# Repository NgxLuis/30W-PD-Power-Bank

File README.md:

# High Performance 30W PD Power Bank (3S 21700)

A professional-grade, high-performance 30W Power Delivery (PD) power bank design. This project features a modular architecture combining fast charging, robust multi-cell battery management, and an efficient synchronous buck controller.

## Technical Specifications

- **Input:** 15W Fast Charging (12.6V/1.2A) via IP2326 Boost Converter architecture.
- **Output:** Up to 30W Power Delivery (PD) via SW3518 Buck Converter.
- **Battery Configuration:** 3S (3 cell) 21700 Li-ion battery pack (approx. 5000mAh/cell, 50Wh total energy capacity).
- **Protection & Management:** Low-side switching BMS powered by BM3451, supporting over-charge, over-discharge, short-circuit, over-current protection, and active cell balancing.
- **Target BOM Budget:** Under 500,000 VND.

## System Architecture & Current Flow

### 1. Charging Mode (Input)
- **IC utilized:** IP2326 (configured for a 3S cell system via a 1kΩ resistor).
- **Current Pathway:** USB-C Input → IP2326 VIN → Internal Boost Switching (via Inductor L2) → VOUT → Battery Cell Positive (+) → Through 3S Battery Cells → Battery Cell Negative (-) → BMS Protection MOSFETs → System Ground (P-) → IP2326 PGND → USB-C Ground return.

### 2. Discharging Mode (Output)
- **IC utilized:** SW3518 (Synchronous Buck Controller).
- **Current Pathway:** Battery Positive (+) → SW3518 VIN → Internal Synchronous Buck Switching (High/Low-side MOSFETs) → Buck Inductor (L1) → Current Shunt Resistor → USB Type-C Port → External Load/Device → Device Ground Return → System Ground (P-) → BMS Protection MOSFETs → Battery Negative (-).

## Hardware Component Configurations
- **IP2326 Charge Current:** Configured via `RISET = 75kΩ` at the ISET pin to cap maximum input charge current at 1.2A.
- **Inductor L2 (Boost):** Requires a saturation current ($I_{SAT}$) of at least 5A.
- **BMS Protection MOSFETs:** Dual NMOS configured with $I_D > 10A$ and ultra-low $R_{DS(on)} < 10mΩ$ to ensure thermal stability and prevent burnout during continuous 3.33A discharge cycles (calculated at the 9V lower cutoff limit).

## Repository Directory Structure
- `/Hardware`: Contains the KiCad schematic (`.kicad_sch`), PCB layout (`.kicad_pcb`), and manufacturing files.
- `/Documentation`: Contains component datasheets and reference files.

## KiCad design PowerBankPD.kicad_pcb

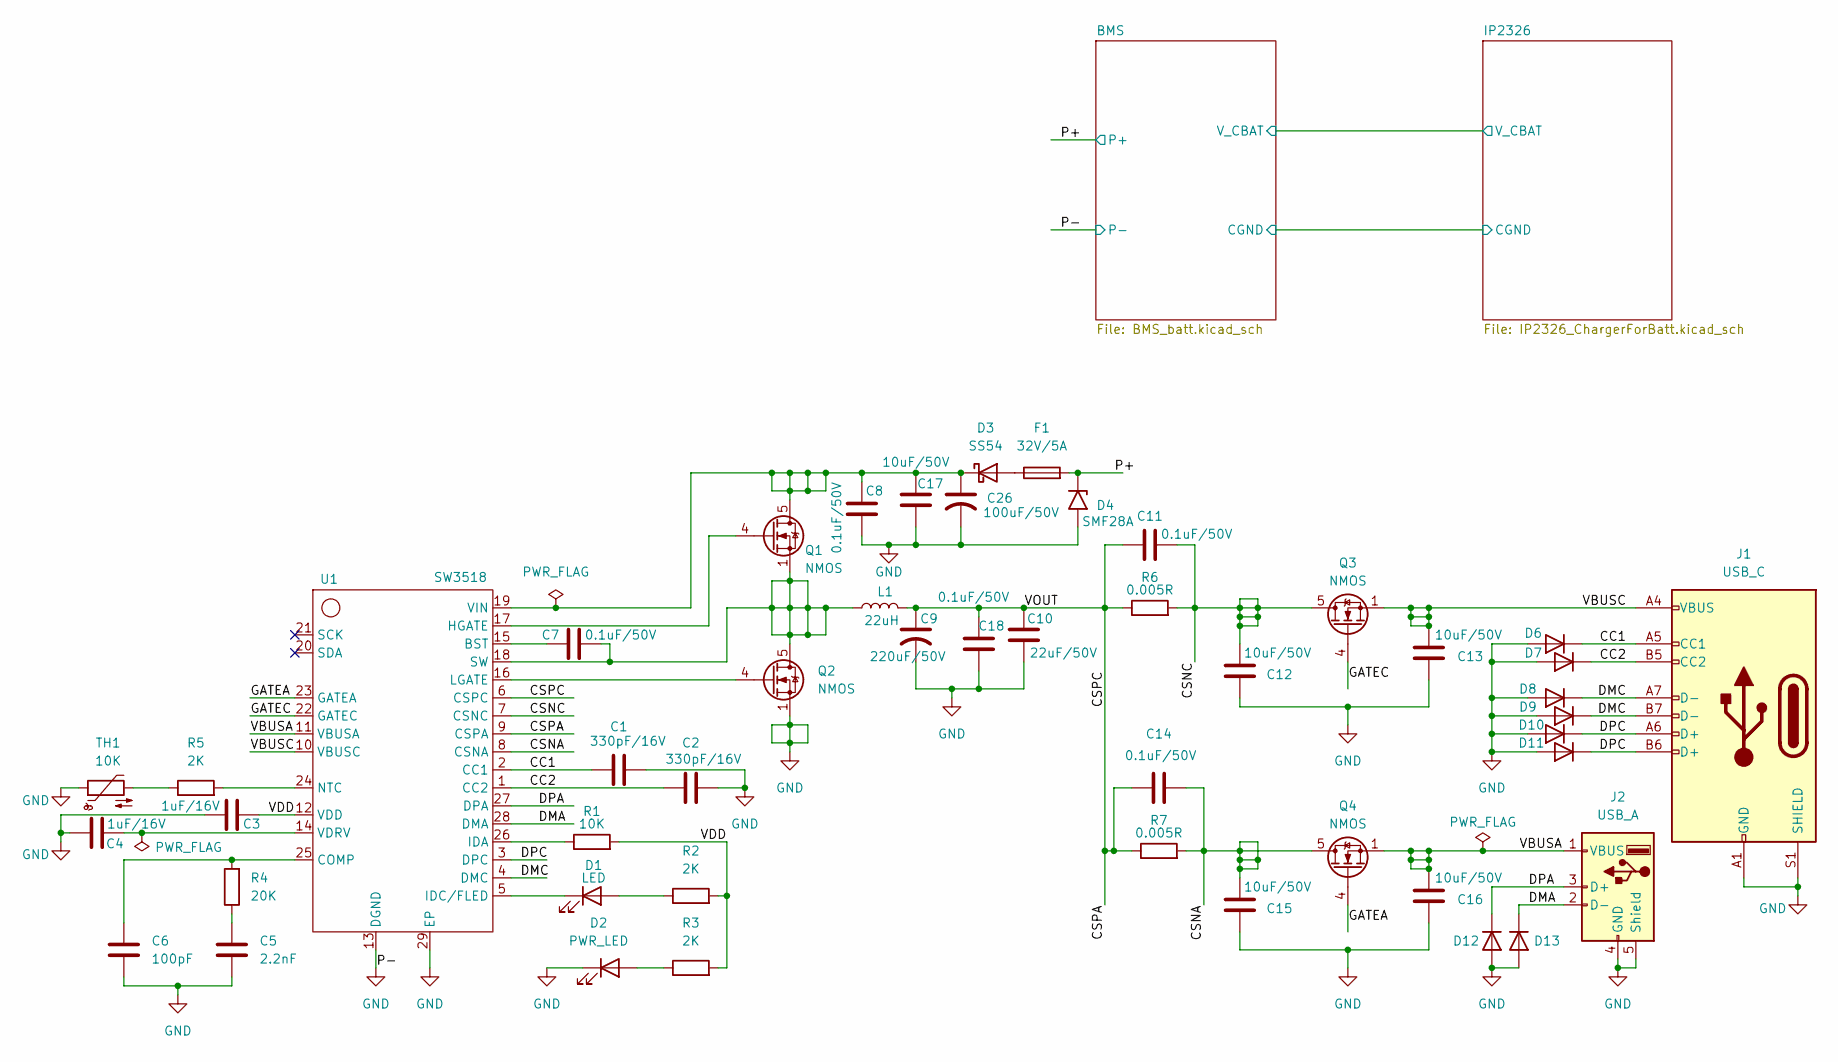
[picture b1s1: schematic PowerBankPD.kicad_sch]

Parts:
C1, C2: 330pF/16V; C_0805_2012Metric
C3, C4: 1uF/16V; C_0805_2012Metric
C5: 2.2nF; C_0805_2012Metric
C6: 100pF; C_0805_2012Metric
C7, C8, C11, C14, C18: 0.1uF/50V; C_0805_2012Metric
C9: 220uF/50V; CP_Elec_8x10
C10: 22uF/50V; C_1210_3225Metric
C12, C13, C15, C16, C17: 10uF/50V; C_1210_3225Metric
C26: 100uF/50V; CP_Elec_8x10
D1: LED; LED_0805_2012Metric
D2: PWR_LED; LED_0805_2012Metric
D3: SS54; D_SMC
D4: SMF28A; D_SMF
D6, D7, D8, D9, D10, D11, D12, D13: D; D_SOD-323
F1: 32V/5A; Fuse_1812_4532Metric
J1: USB_C; USB_C_Receptacle_HRO_TYPE-C-31-M-12
J2: USB_A; USB_A_TE_292303-7_Horizontal
L1: 22uH; L_12x12mm_H8mm
Q1, Q2, Q3, Q4: NMOS; HSOP-8-1EP_3.9x4.9mm_P1.27mm_EP2.41x3.1mm
R1: 10K; R_0805_2012Metric
R2, R3, R5: 2K; R_0805_2012Metric
R4: 20K; R_0805_2012Metric
R6, R7: 0.005R; R_2512_6332Metric
TH1: 10K; R_0805_2012Metric
U1: SW3518; SW3518_Power100W

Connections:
/CC1: C1.1, D6.1 (K), J1.A5 (CC1), U1.2 (CC1)
/CC2: C2.1, D7.1 (K), J1.B5 (CC2), U1.1 (CC2)
/CSNA: C14.2, C15.2, Q4.5 (D), R7.2, U1.8 (CSNA)
/CSNC: C11.2, C12.2, Q3.5 (D), R6.2, U1.7 (CSNC)
/CSPA: C9.1, C10.1, C11.1, C14.1, C18.1, L1.2, R6.1, R7.1, U1.6 (CSPC), U1.9 (CSPA)
/DMA: D13.1 (K), J2.2 (D-), U1.28 (DMA)
/DMC: D8.1 (K), D9.1 (K), J1.A7 (D-), J1.B7 (D-), U1.4 (DMC)
/DPA: D12.1 (K), J2.3 (D+), U1.27 (DPA)
/DPC: D10.1 (K), D11.1 (K), J1.A6 (D+), J1.B6 (D+), U1.3 (DPC)
/GATEA: Q4.4 (G), U1.23 (GATEA)
/GATEC: Q3.4 (G), U1.22 (GATEC)
/P+: D4.1 (A1), F1.2; also elsewhere on the board
/VBUSA: C16.2, J2.1 (VBUS), Q4.1 (S), Q4.2 (S), Q4.3 (S), U1.11 (VBUSA)
/VBUSC: C13.2, J1.A4 (VBUS), J1.A9 (VBUS), J1.B4 (VBUS), J1.B9 (VBUS), Q3.1 (S), Q3.2 (S), Q3.3 (S), U1.10 (VBUSC)
/VDD: C3.2, R1.2, R2.2, R3.2, U1.12 (VDD)
GND: C1.2, C2.2, C3.1, C4.1, C5.1, C6.1, C8.2, C9.2, C10.2, C12.1, C13.1, C15.1, C16.1, C17.2, C18.2, C26.2, D2.1 (K), D4.2 (A2), D6.2 (A), D7.2 (A), D8.2 (A), D9.2 (A), D10.2 (A), D11.2 (A), D12.2 (A), D13.2 (A), J1.A1 (GND), J1.A12 (GND), J1.B1 (GND), J1.B12 (GND), J1.S1 (SHIELD), J2.4 (GND), J2.5 (Shield), Q2.1 (S), Q2.2 (S), Q2.3 (S), TH1.1, U1.13 (DGND), U1.29 (EP); also elsewhere on the board
unnamed: C5.2, R4.1
unnamed: D1.2 (A), R2.1
unnamed: D1.1 (K), U1.5 (IDC/FLED)
unnamed: D2.2 (A), R3.1
unnamed: D3.2 (A), F1.1
unnamed: C8.1, C17.1, C26.1, D3.1 (K), Q1.5 (D), U1.19 (VIN)
unnamed: Q1.4 (G), U1.17 (HGATE)
unnamed: C7.2, L1.1, Q1.1 (S), Q1.2 (S), Q1.3 (S), Q2.5 (D), U1.18 (SW)
unnamed: Q2.4 (G), U1.16 (LGATE)
unnamed: R5.1, TH1.2
unnamed: C7.1, U1.15 (BST)
unnamed: C6.2, R4.2, U1.25 (COMP)
unnamed: R1.1, U1.26 (IDA)
unnamed: R5.2, U1.24 (NTC)
unnamed: C4.2, U1.14 (VDRV)

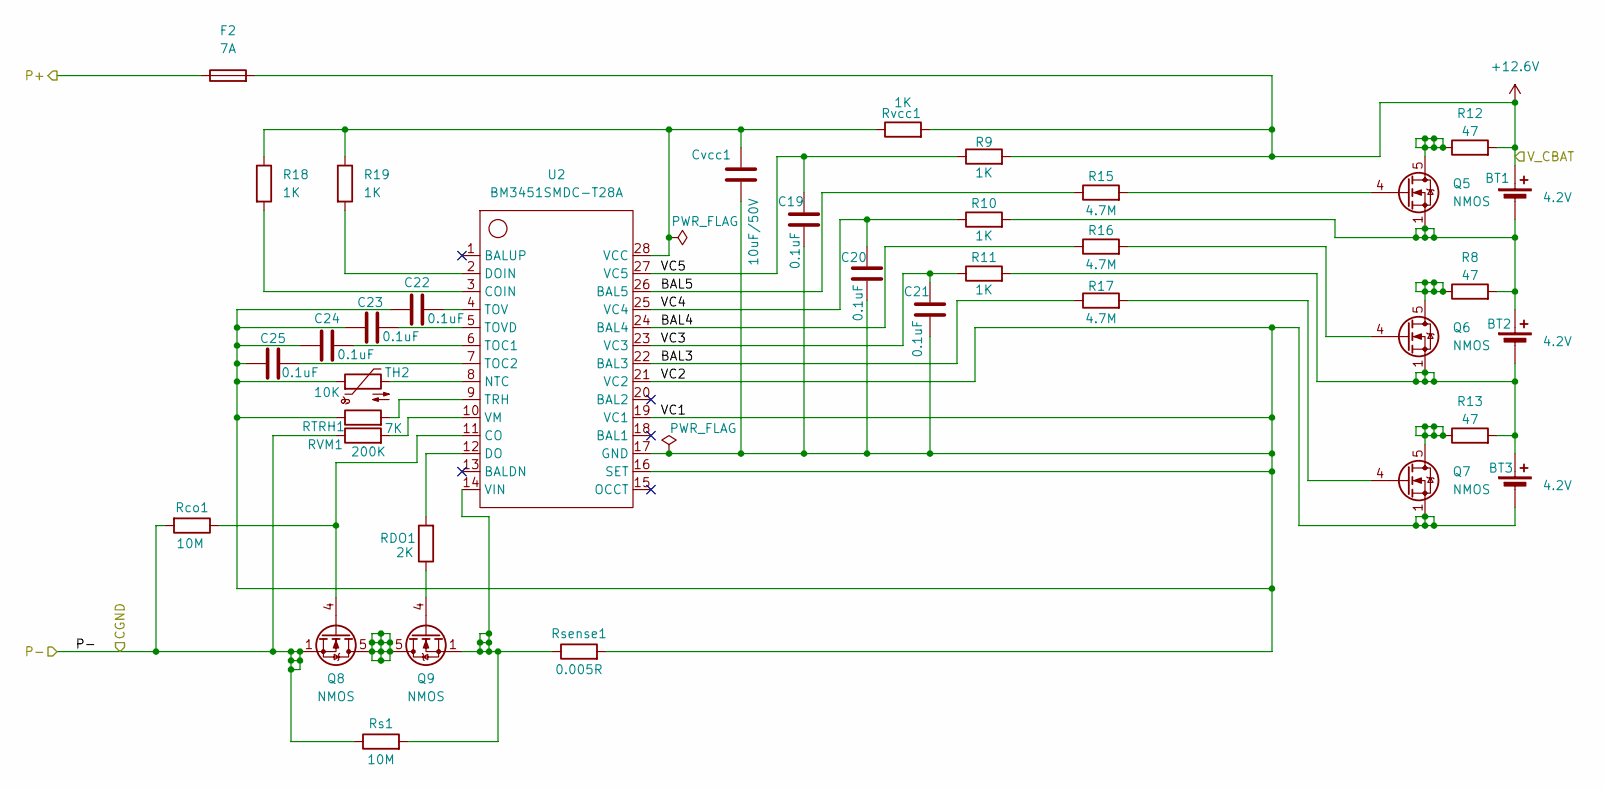
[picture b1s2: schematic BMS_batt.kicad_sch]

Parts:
BT1, BT2, BT3: 4.2V; 2_Pin_Battery
C19, C20, C21, C22, C23, C24, C25: 0.1uF; C_0805_2012Metric
Cvcc1: 10uF/50V; C_1210_3225Metric
F2: 7A; Fuse_1812_4532Metric
Q5, Q6, Q7, Q8, Q9: NMOS; HSOP-8-1EP_3.9x4.9mm_P1.27mm_EP2.41x3.1mm
R8, R12, R13: 47; R_0805_2012Metric
R9, R10, R11, R18, R19: 1K; R_0805_2012Metric
R15, R16, R17: 4.7M; R_0805_2012Metric
RDO1: 2K; R_0805_2012Metric
RTRH1: 7K; R_0805_2012Metric
RVM1: 200K; R_0805_2012Metric
Rco1: 10M; R_0805_2012Metric
Rs1: 10M; R_0805_2012Metric
Rsense1: 0.005R; R_2512_6332Metric
Rvcc1: 1K; R_0805_2012Metric
TH2: 10K; R_0805_2012Metric
U2: BM3451SMDC-T28A; BM3451

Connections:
+12.6V: BT1.1 (+), F2.2, R9.2, R12.2, Rvcc1.2; also elsewhere on the board
/BMS/BAL3: R17.1, U2.22 (BAL3)
/BMS/BAL4: R16.1, U2.24 (BAL4)
/BMS/BAL5: R15.1, U2.26 (BAL5)
/BMS/VC1: BT3.2 (-), C19.2, C20.2, C21.2, C22.1, C23.1, C24.1, C25.1, Cvcc1.2, Q7.1 (S), Q7.2 (S), Q7.3 (S), RTRH1.1, Rsense1.2, TH2.1, U2.16 (SET), U2.17 (GND), U2.19 (VC1), U2.21 (VC2)
/BMS/VC3: C21.1, R11.1, U2.23 (VC3)
/BMS/VC4: C20.1, R10.1, U2.25 (VC4)
/BMS/VC5: C19.1, R9.1, U2.27 (VC5)
/P+: F2.1; also elsewhere on the board
GND: Q8.1 (S), Q8.2 (S), Q8.3 (S), RVM1.1, Rco1.2, Rs1.1; also elsewhere on the board
unnamed 27: BT1.2 (-), BT2.1 (+), Q5.1 (S), Q5.2 (S), Q5.3 (S), R8.2, R10.2; also elsewhere on the board
unnamed 28: BT2.2 (-), BT3.1 (+), Q6.1 (S), Q6.2 (S), Q6.3 (S), R11.2, R13.2; also elsewhere on the board
unnamed: Q5.5 (D), R12.1
unnamed: Q5.4 (G), R15.2
unnamed: Q6.5 (D), R8.1
unnamed: Q6.4 (G), R16.2
unnamed: Q7.5 (D), R13.1
unnamed: Q7.4 (G), R17.2
unnamed: Q8.5 (D), Q9.5 (D)
unnamed: Q8.4 (G), Rco1.1, U2.11 (CO)
unnamed: Q9.4 (G), RDO1.1
unnamed: R18.2, U2.3 (COIN)
unnamed: RDO1.2, U2.12 (DO)
unnamed: R19.2, U2.2 (DOIN)
unnamed: TH2.2, U2.8 (NTC)
unnamed: C24.2, U2.6 (TOC1)
unnamed: C25.2, U2.7 (TOC2)
unnamed: C22.2, U2.4 (TOV)
unnamed: C23.2, U2.5 (TOVD)
unnamed: RTRH1.2, U2.9 (TRH)
unnamed: Cvcc1.1, R18.1, R19.1, Rvcc1.1, U2.28 (VCC)
unnamed: Q9.1 (S), Q9.2 (S), Q9.3 (S), Rs1.2, Rsense1.1, U2.14 (VIN)
unnamed: RVM1.2, U2.10 (VM)

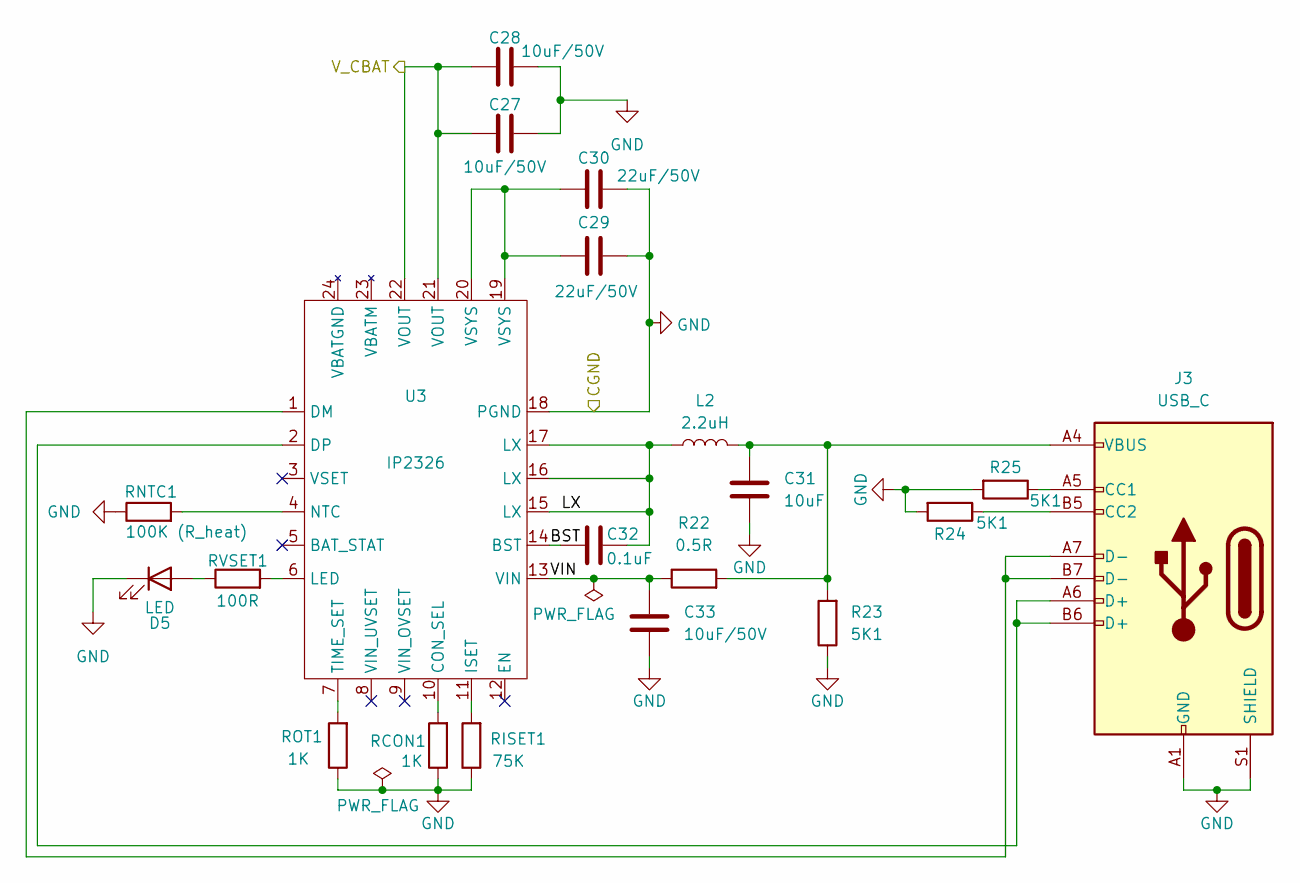
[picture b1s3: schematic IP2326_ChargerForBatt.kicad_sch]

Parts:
C27, C28, C33: 10uF/50V; C_1210_3225Metric
C29, C30: 22uF/50V; C_1210_3225Metric
C31: 10uF; C_1210_3225Metric
C32: 0.1uF; C_0805_2012Metric
D5: LED; LED_0805_2012Metric
J3: USB_C; USB_C_Receptacle_HRO_TYPE-C-31-M-12
L2: 2.2uH; L_12x12mm_H8mm
R22: 0.5R; R_1206_3216Metric
R23, R24, R25: 5K1; R_0805_2012Metric
RCON1: 1K; R_0805_2012Metric
RISET1: 75K; R_0805_2012Metric
RNTC1: 100K (R_heat); R_0805_2012Metric
ROT1: 1K; R_0805_2012Metric
RVSET1: 100R; R_0805_2012Metric
U3: IP2326; IP2326_Power18W

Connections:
+12.6V: C27.1, C28.1, U3.21 (VOUT), U3.22 (VOUT); also elsewhere on the board
/IP2326/BST: C32.1, U3.14 (BST)
/IP2326/LX: C32.2, L2.1, U3.15 (LX), U3.16 (LX), U3.17 (LX)
/IP2326/VIN: C33.1, R22.1, U3.13 (VIN)
GND: C27.2, C28.2, C29.2, C30.2, C31.2, C33.2, D5.1 (K), J3.A1 (GND), J3.A12 (GND), J3.B1 (GND), J3.B12 (GND), J3.S1 (SHIELD), R23.1, R24.2, R25.2, RCON1.1, RISET1.1, RNTC1.1, ROT1.1, U3.18 (PGND); also elsewhere on the board
unnamed: C29.1, C30.1, U3.19 (VSYS), U3.20 (VSYS)
unnamed: C31.1, J3.A4 (VBUS), J3.A9 (VBUS), J3.B4 (VBUS), J3.B9 (VBUS), L2.2, R22.2, R23.2
unnamed: D5.2 (A), RVSET1.1
unnamed: J3.A5 (CC1), R25.1
unnamed: J3.B5 (CC2), R24.1
unnamed: RCON1.2, U3.10 (CON_SEL)
unnamed: J3.A7 (D-), J3.B7 (D-), U3.1 (DM)
unnamed: J3.A6 (D+), J3.B6 (D+), U3.2 (DP)
unnamed: RISET1.2, U3.11 (ISET)
unnamed: RVSET1.2, U3.6 (LED)
unnamed: RNTC1.2, U3.4 (NTC)
unnamed: ROT1.2, U3.7 (TIME_SET)

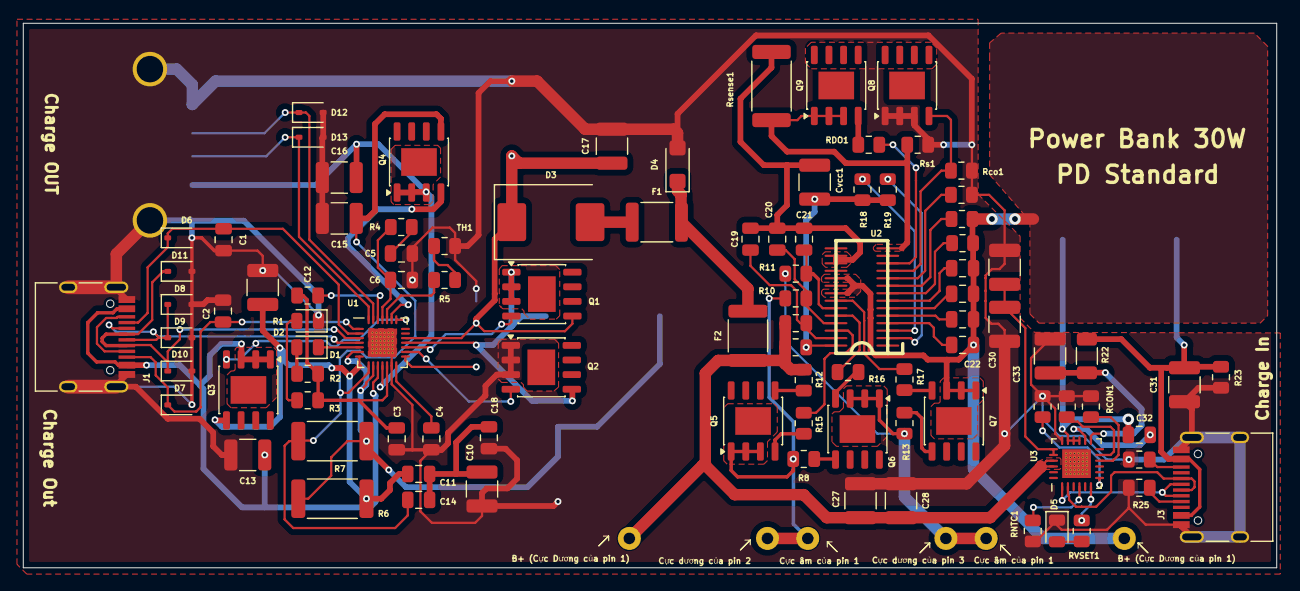
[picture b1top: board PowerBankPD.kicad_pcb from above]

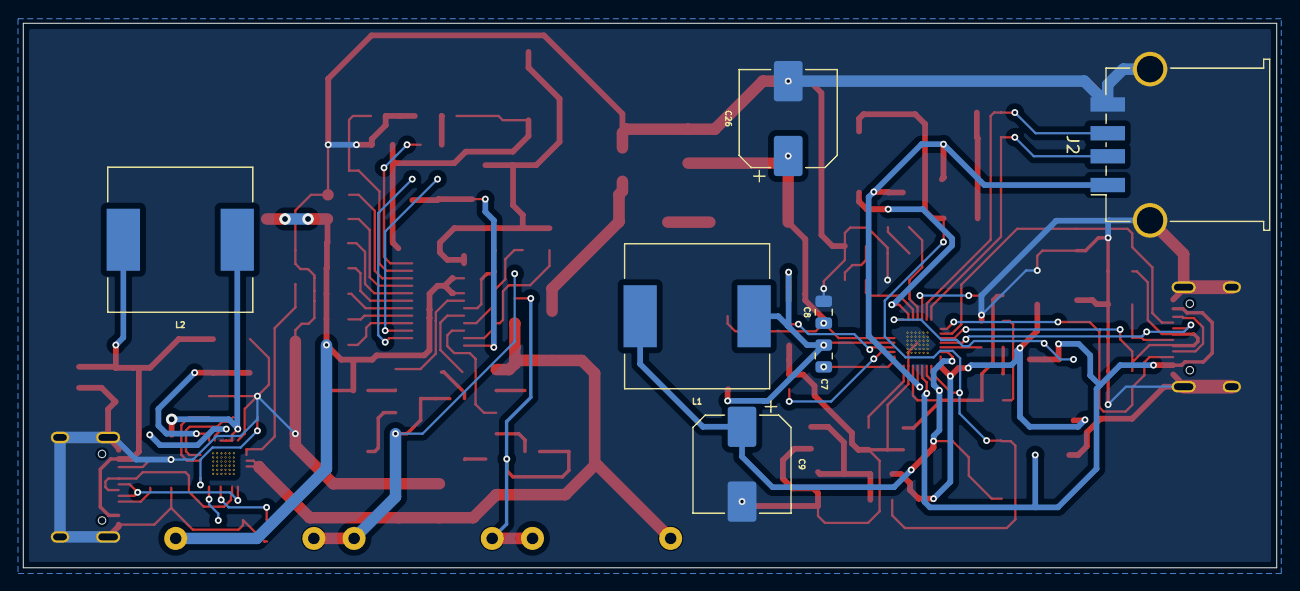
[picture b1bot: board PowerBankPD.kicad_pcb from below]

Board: 2 copper layers, 108.9 x 47.3 mm, 105 parts (7 on the bottom side), 77 nets.

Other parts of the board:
B+ (Cực Dương của pin 1): 4.2V; 2_Pin_Battery
Cực dương của pin 2: 4.2V; 2_Pin_Battery

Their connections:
+12.6V: B+ (Cực Dương của pin 1).1 (+); also elsewhere on the board
unnamed 27: B+ (Cực Dương của pin 1).2 (-), Cực dương của pin 2.1 (+); also elsewhere on the board
unnamed 28: Cực dương của pin 2.2 (-); also elsewhere on the board
